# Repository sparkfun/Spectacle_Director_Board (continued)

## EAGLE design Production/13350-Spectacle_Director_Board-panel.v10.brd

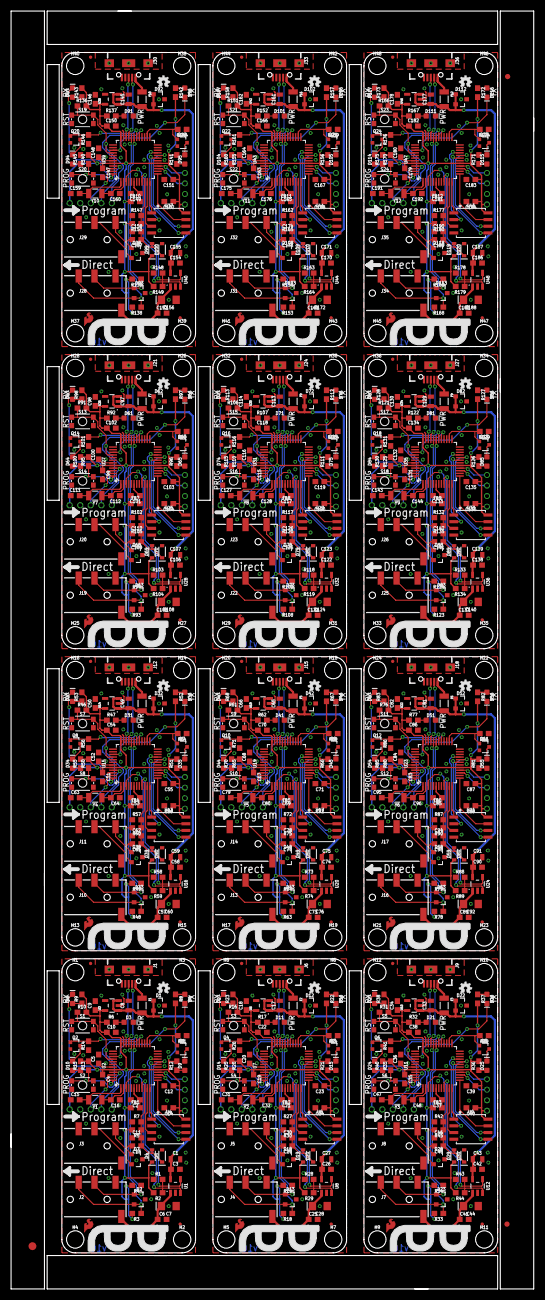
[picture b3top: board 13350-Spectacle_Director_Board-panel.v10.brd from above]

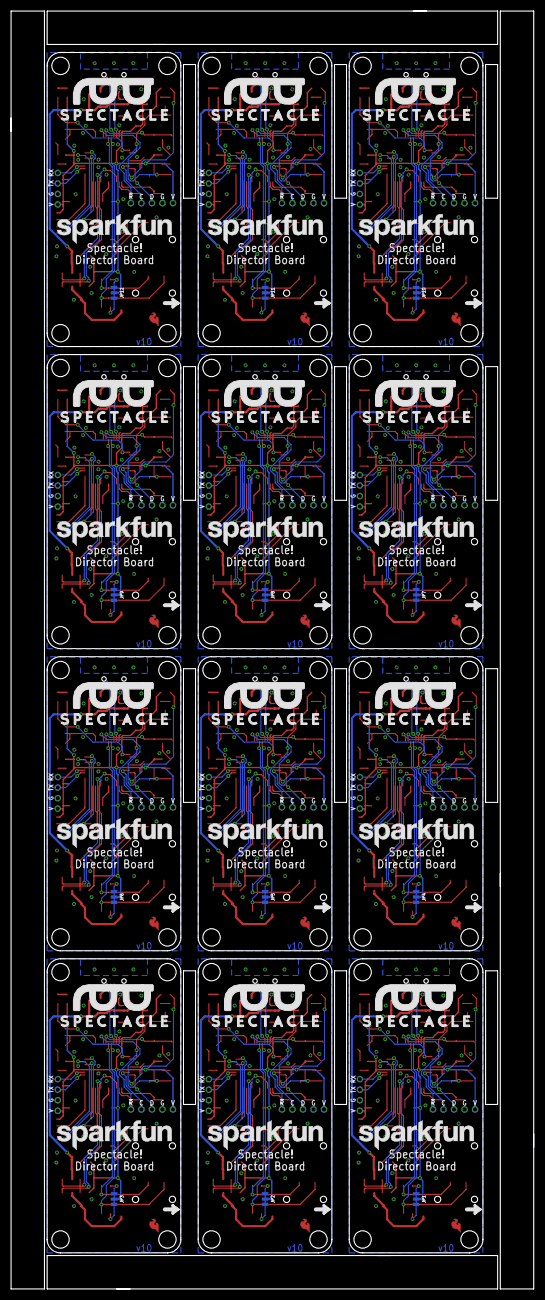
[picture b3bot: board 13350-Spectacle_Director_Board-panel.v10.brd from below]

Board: 2 copper layers, 99.3 x 242.8 mm, 891 parts (132 on the bottom side), 528 nets.

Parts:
C1, C27, C43, C59, C75, C91, C107, C123, C139, C155, C171, C187: 10uF; 0805
C2, C3, C4, C5, C6, C10, C12, C14, C19, C20, C21, C22, C23, C24, C25, C26, C35, C36, C37, C38, C39, C40, C41, C42, C51, C52, C53, C54, C55, C56, C57, C58, C67, C68, C69, C70, C71, C72, C73, C74, C83, C84, C85, C86, C87, C88, C89, C90, C99, C100, C101, C102, C103, C104, C105, C106, C115, C116, C117, C118, C119, C120, C121, C122, C131, C132, C133, C134, C135, C136, C137, C138, C147, C148, C149, C150, C151, C152, C153, C154, C163, C164, C165, C166, C167, C168, C169, C170, C179, C180, C181, C182, C183, C184, C185, C186: 0.1uF; 0603
C7, C28, C44, C60, C76, C92, C108, C124, C140, C156, C172, C188: 10uF; EIA3216
C8, C17, C33, C49, C65, C81, C97, C113, C129, C145, C161, C177: 1.0uF; 0805
C9, C18, C34, C50, C66, C82, C98, C114, C130, C146, C162, C178: 2.2uF; 0603
C11, C30, C46, C62, C78, C94, C110, C126, C142, C158, C174, C190: 47pF; 0603
C13, C29, C45, C61, C77, C93, C109, C125, C141, C157, C173, C189: 0.22uF; 0603
C15, C16, C31, C32, C47, C48, C63, C64, C79, C80, C95, C96, C111, C112, C127, C128, C143, C144, C159, C160, C175, C176, C191, C192: 15pF; 0603
D1, D2, D7, D12, D13, D18, D22, D23, D28, D32, D33, D38, D42, D43, D48, D52, D53, D58, D62, D63, D68, D72, D73, D78, D82, D83, D88, D92, D93, D98, D102, D103, D108, D112, D113, D118: PESD1CAN; SOT23-3
D3, D11, D21, D31, D41, D51, D61, D71, D81, D91, D101, D111: RED; LED-0603
D4, D5, D19, D20, D29, D30, D39, D40, D49, D50, D59, D60, D69, D70, D79, D80, D89, D90, D99, D100, D109, D110, D119, D120: 0.5A/40V/420mV; SOD-323
D6, D10, D14, D16, D24, D26, D34, D36, D44, D46, D54, D56, D64, D66, D74, D76, D84, D86, D94, D96, D104, D106, D114, D116: GREEN; LED-0603
D8, D17, D27, D37, D47, D57, D67, D77, D87, D97, D107, D117: Yellow; LED-0603
D9, D15, D25, D35, D45, D55, D65, D75, D85, D95, D105, D115: BLUE; LED-0603
E$1: FIDUCIAL-1.5X3
E$4, E$7: FIDUCIAL-1X2
F1, F2, F3, F4, F5, F6, F7, F8, F9, F10, F11, F12: 500mA; PTC-1206
FB1, FB2, FB3, FB4, FB5, FB6, FB7, FB8, FB9, FB10, FB11, FB12: 30Ω/1.8A; 0603
FD1, FD2, FD3, FD4, FD5, FD6, FD7, FD8, FD9, FD10, FD11, FD12, FD13, FD14, FD15, FD16, FD17, FD18, FD19, FD20, FD21, FD22, FD23, FD24: FIDUCIALUFIDUCIAL; FIDUCIAL-MICRO
H1, H2, H3, H4, H5, H6, H7, H8, H9, H10, H11, H12, H13, H14, H15, H16, H17, H18, H19, H20, H21, H22, H23, H24, H25, H26, H27, H28, H29, H30, H31, H32, H33, H34, H35, H36, H37, H38, H39, H40, H41, H42, H43, H44, H45, H46, H47, H48: STAND-OFF
J1, J6, J9, J12, J15, J18, J21, J24, J27, J30, J33, J36: USB-B-MICRO-SMD
J2, J4, J7, J10, J13, J16, J19, J22, J25, J28, J31, J34: I2C-TRRS; AUDIO_JACK_3.5MM_TRRS_SMD_RA
J3, J5, J8, J11, J14, J17, J20, J23, J26, J29, J32, J35: Serial-TRRS; AUDIO_JACK_3.5MM_TRRS_SMD_RA
JP1, JP2, JP3, JP4, JP5, JP6, JP7, JP8, JP9, JP10, JP11, JP12: JUMPER-SMT_3_2-NC_TRACE_NO-SILK; SMT-JUMPER_3_2-NC_TRACE_NO-SILK
LOGO1, LOGO5, LOGO8, LOGO11, LOGO14, LOGO17, LOGO20, LOGO23, LOGO26, LOGO29, LOGO32, LOGO35: OSHW-LOGOMINI; OSHW-LOGO-MINI
LOGO2, LOGO4, LOGO7, LOGO10, LOGO13, LOGO16, LOGO19, LOGO22, LOGO25, LOGO28, LOGO31, LOGO34: SFE_LOGO_NAME.2_INCH; SFE_LOGO_NAME_.2
LOGO3, LOGO6, LOGO9, LOGO12, LOGO15, LOGO18, LOGO21, LOGO24, LOGO27, LOGO30, LOGO33, LOGO36: SFE_LOGO_FLAME.1COP; SFE_LOGO_FLAME_COPPER_.1
Q1, Q2, Q3, Q4, Q5, Q6, Q7, Q8, Q9, Q10, Q11, Q12, Q13, Q14, Q15, Q16, Q17, Q18, Q19, Q20, Q21, Q22, Q23, Q24: 310mA/60V/1.6Ω; SOT323
R1, R11, R14, R24, R26, R28, R39, R41, R43, R54, R56, R58, R69, R71, R73, R84, R86, R88, R99, R101, R103, R114, R116, R118, R129, R131, R133, R144, R146, R148, R159, R161, R163, R174, R176, R178: 100k; 0603
R2, R5, R7, R10, R13, R16, R20, R27, R29, R30, R31, R35, R42, R44, R45, R46, R50, R57, R59, R60, R61, R65, R72, R74, R75, R76, R80, R87, R89, R90, R91, R95, R102, R104, R105, R106, R110, R117, R119, R120, R121, R125, R132, R134, R135, R136, R140, R147, R149, R150, R151, R155, R162, R164, R165, R166, R170, R177, R179, R180: 10k; 0603
R3, R4, R18, R19, R33, R34, R48, R49, R63, R64, R78, R79, R93, R94, R108, R109, R123, R124, R138, R139, R153, R154, R168, R169: 2.2k; 0603
R6, R17, R32, R47, R62, R77, R92, R107, R122, R137, R152, R167: 1k; 0603
R8, R9, R12, R15, R21, R22, R23, R25, R36, R37, R38, R40, R51, R52, R53, R55, R66, R67, R68, R70, R81, R82, R83, R85, R96, R97, R98, R100, R111, R112, R113, R115, R126, R127, R128, R130, R141, R142, R143, R145, R156, R157, R158, R160, R171, R172, R173, R175: 330; 0603
S1, S3, S5, S7, S9, S11, S13, S15, S17, S19, S21, S23: RESET; TACTILE_SWITCH_SMD_4.6X2.8MM
S2, S4, S6, S8, S10, S12, S14, S16, S18, S20, S22, S24: BTN2; TACTILE_SWITCH_SMD_4.6X2.8MM
TP1, TP10, TP19, TP28, TP37, TP46, TP55, TP64, TP73, TP82, TP91, TP100: TP-SWDIO; PAD.03X.05
TP2, TP11, TP20, TP29, TP38, TP47, TP56, TP65, TP74, TP83, TP92, TP101: TP-SWCLK; PAD.03X.05
TP3, TP12, TP21, TP30, TP39, TP48, TP57, TP66, TP75, TP84, TP93, TP102: TP-!RESET!; PAD.03X.05
TP4, TP13, TP22, TP31, TP40, TP49, TP58, TP67, TP76, TP85, TP94, TP103: TP-3.3V; PAD.03X.05
TP5, TP6, TP7, TP8, TP9, TP14, TP15, TP16, TP17, TP18, TP23, TP24, TP25, TP26, TP27, TP32, TP33, TP34, TP35, TP36, TP41, TP42, TP43, TP44, TP45, TP50, TP51, TP52, TP53, TP54, TP59, TP60, TP61, TP62, TP63, TP68, TP69, TP70, TP71, TP72, TP77, TP78, TP79, TP80, TP81, TP86, TP87, TP88, TP89, TP90, TP95, TP96, TP97, TP98, TP99, TP104, TP105, TP106, TP107, TP108: TP-GND; PAD.03X.05
U1, U8, U12, U16, U20, U24, U28, U32, U36, U40, U44, U48: AP2151; SOT23-5
U2, U7, U11, U15, U19, U23, U27, U31, U35, U39, U43, U47: ATSAMD21G-A; TQFP-48
U3, U6, U10, U14, U18, U22, U26, U30, U34, U38, U42, U46: 3.3V; SOT23-5
U4, U5, U9, U13, U17, U21, U25, U29, U33, U37, U41, U45: W25Q32FV; SOIC-8
Y1, Y2, Y3, Y4, Y5, Y6, Y7, Y8, Y9, Y10, Y11, Y12: 32.768kHz; CRYSTAL-SMD-3.2X1.5MM

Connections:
3.3V: C4.1, C9.1, C10.1, C12.1, C14.1, D4.C, FB1.1, JP1.2, R2.2, R5.2, R6.1, R8.2, R9.2, R10.2, R12.2, R13.2, R15.2, TP4.P$1, TP6.P$1, U2.17, U2.36, U2.44, U3.5, U4.8
3.3V1: C18.1, C19.1, C22.1, C23.1, C24.1, D19.C, FB2.1, JP2.2, R16.2, R17.1, R20.2, R21.2, R22.2, R23.2, R25.2, R29.2, R30.2, TP13.P$1, TP15.P$1, U5.8, U6.5, U7.17, U7.36, U7.44
3.3V2: C34.1, C35.1, C38.1, C39.1, C40.1, D29.C, FB3.1, JP3.2, R31.2, R32.1, R35.2, R36.2, R37.2, R38.2, R40.2, R44.2, R45.2, TP22.P$1, TP24.P$1, U9.8, U10.5, U11.17, U11.36, U11.44
3.3V3: C50.1, C51.1, C54.1, C55.1, C56.1, D39.C, FB4.1, JP4.2, R46.2, R47.1, R50.2, R51.2, R52.2, R53.2, R55.2, R59.2, R60.2, TP31.P$1, TP33.P$1, U13.8, U14.5, U15.17, U15.36, U15.44
3.3V4: C66.1, C67.1, C70.1, C71.1, C72.1, D49.C, FB5.1, JP5.2, R61.2, R62.1, R65.2, R66.2, R67.2, R68.2, R70.2, R74.2, R75.2, TP40.P$1, TP42.P$1, U17.8, U18.5, U19.17, U19.36, U19.44
3.3V5: C82.1, C83.1, C86.1, C87.1, C88.1, D59.C, FB6.1, JP6.2, R76.2, R77.1, R80.2, R81.2, R82.2, R83.2, R85.2, R89.2, R90.2, TP49.P$1, TP51.P$1, U21.8, U22.5, U23.17, U23.36, U23.44
3.3V6: C98.1, C99.1, C102.1, C103.1, C104.1, D69.C, FB7.1, JP7.2, R91.2, R92.1, R95.2, R96.2, R97.2, R98.2, R100.2, R104.2, R105.2, TP58.P$1, TP60.P$1, U25.8, U26.5, U27.17, U27.36, U27.44
3.3V7: C114.1, C115.1, C118.1, C119.1, C120.1, D79.C, FB8.1, JP8.2, R106.2, R107.1, R110.2, R111.2, R112.2, R113.2, R115.2, R119.2, R120.2, TP67.P$1, TP69.P$1, U29.8, U30.5, U31.17, U31.36, U31.44
3.3V8: C130.1, C131.1, C134.1, C135.1, C136.1, D89.C, FB9.1, JP9.2, R121.2, R122.1, R125.2, R126.2, R127.2, R128.2, R130.2, R134.2, R135.2, TP76.P$1, TP78.P$1, U33.8, U34.5, U35.17, U35.36, U35.44
3.3V9: C146.1, C147.1, C150.1, C151.1, C152.1, D99.C, FB10.1, JP10.2, R136.2, R137.1, R140.2, R141.2, R142.2, R143.2, R145.2, R149.2, R150.2, TP85.P$1, TP87.P$1, U37.8, U38.5, U39.17, U39.36, U39.44
3.3V10: C162.1, C163.1, C166.1, C167.1, C168.1, D109.C, FB11.1, JP11.2, R151.2, R152.1, R155.2, R156.2, R157.2, R158.2, R160.2, R164.2, R165.2, TP94.P$1, TP96.P$1, U41.8, U42.5, U43.17, U43.36, U43.44
3.3V11: C178.1, C179.1, C182.1, C183.1, C184.1, D119.C, FB12.1, JP12.2, R166.2, R167.1, R170.2, R171.2, R172.2, R173.2, R175.2, R179.2, R180.2, TP103.P$1, TP105.P$1, U45.8, U46.5, U47.17, U47.36, U47.44
!RESET: R10.1, S1.3, S1.4, TP3.P$1, U2.40
!RESET1: R16.1, S3.3, S3.4, TP12.P$1, U7.40
!RESET2: R31.1, S5.3, S5.4, TP21.P$1, U11.40
!RESET3: R46.1, S7.3, S7.4, TP30.P$1, U15.40
!RESET4: R61.1, S9.3, S9.4, TP39.P$1, U19.40
!RESET5: R76.1, S11.3, S11.4, TP48.P$1, U23.40
!RESET6: R91.1, S13.3, S13.4, TP57.P$1, U27.40
!RESET7: R106.1, S15.3, S15.4, TP66.P$1, U31.40
!RESET8: R121.1, S17.3, S17.4, TP75.P$1, U35.40
!RESET9: R136.1, S19.3, S19.4, TP84.P$1, U39.40
!RESET10: R151.1, S21.3, S21.4, TP93.P$1, U43.40
!RESET11: R166.1, S23.3, S23.4, TP102.P$1, U47.40
A1_FSK-RX: C11.2, C13.1, D4.A, D5.C, R5.1, R7.2, U2.10
A1_FSK-RX1: C29.1, C30.2, D19.A, D20.C, R27.2, R30.1, U7.10
A1_FSK-RX2: C45.1, C46.2, D29.A, D30.C, R42.2, R45.1, U11.10
A1_FSK-RX3: C61.1, C62.2, D39.A, D40.C, R57.2, R60.1, U15.10
A1_FSK-RX4: C77.1, C78.2, D49.A, D50.C, R72.2, R75.1, U19.10
A1_FSK-RX5: C93.1, C94.2, D59.A, D60.C, R87.2, R90.1, U23.10
A1_FSK-RX6: C109.1, C110.2, D69.A, D70.C, R102.2, R105.1, U27.10
A1_FSK-RX7: C125.1, C126.2, D79.A, D80.C, R117.2, R120.1, U31.10
A1_FSK-RX8: C141.1, C142.2, D89.A, D90.C, R132.2, R135.1, U35.10
A1_FSK-RX9: C157.1, C158.2, D99.A, D100.C, R147.2, R150.1, U39.10
A1_FSK-RX10: C173.1, C174.2, D109.A, D110.C, R162.2, R165.1, U43.10
A1_FSK-RX11: C189.1, C190.2, D119.A, D120.C, R177.2, R180.1, U47.10
A3_VOUT_EN: R1.2, U1.4, U2.9
A3_VOUT_EN1: R28.2, U7.9, U8.4
A3_VOUT_EN2: R43.2, U11.9, U12.4
A3_VOUT_EN3: R58.2, U15.9, U16.4
A3_VOUT_EN4: R73.2, U19.9, U20.4
A3_VOUT_EN5: R88.2, U23.9, U24.4
A3_VOUT_EN6: R103.2, U27.9, U28.4
A3_VOUT_EN7: R118.2, U31.9, U32.4
A3_VOUT_EN8: R133.2, U35.9, U36.4
A3_VOUT_EN9: R148.2, U39.9, U40.4
A3_VOUT_EN10: R163.2, U43.9, U44.4
A3_VOUT_EN11: R178.2, U47.9, U48.4
A4_VOUT_FLG: R2.1, U1.3, U2.3
A4_VOUT_FLG1: R29.1, U7.3, U8.3
A4_VOUT_FLG2: R44.1, U11.3, U12.3
A4_VOUT_FLG3: R59.1, U15.3, U16.3
A4_VOUT_FLG4: R74.1, U19.3, U20.3
A4_VOUT_FLG5: R89.1, U23.3, U24.3
A4_VOUT_FLG6: R104.1, U27.3, U28.3
A4_VOUT_FLG7: R119.1, U31.3, U32.3
A4_VOUT_FLG8: R134.1, U35.3, U36.3
A4_VOUT_FLG9: R149.1, U39.3, U40.3
A4_VOUT_FLG10: R164.1, U43.3, U44.3
A4_VOUT_FLG11: R179.1, U47.3, U48.3
D0/RXI: TP8.P$1, U2.16
D0/RXI1: TP17.P$1, U7.16
D0/RXI2: TP26.P$1, U11.16
D0/RXI3: TP35.P$1, U15.16
D0/RXI4: TP44.P$1, U19.16
D0/RXI5: TP53.P$1, U23.16
D0/RXI6: TP62.P$1, U27.16
D0/RXI7: TP71.P$1, U31.16
D0/RXI8: TP80.P$1, U35.16
D0/RXI9: TP89.P$1, U39.16
D0/RXI10: TP98.P$1, U43.16
D0/RXI11: TP107.P$1, U47.16
D1/TXO: TP7.P$1, U2.15
D1/TXO1: TP16.P$1, U7.15
D1/TXO2: TP25.P$1, U11.15
D1/TXO3: TP34.P$1, U15.15
D1/TXO4: TP43.P$1, U19.15
D1/TXO5: TP52.P$1, U23.15
D1/TXO6: TP61.P$1, U27.15
D1/TXO7: TP70.P$1, U31.15
D1/TXO8: TP79.P$1, U35.15
D1/TXO9: TP88.P$1, U39.15
D1/TXO10: TP97.P$1, U43.15
D1/TXO11: TP106.P$1, U47.15
D4_FLASH!HD!: U2.13, U4.7
D4_FLASH!HD!1: U5.7, U7.13
D4_FLASH!HD!2: U9.7, U11.13
D4_FLASH!HD!3: U13.7, U15.13
D4_FLASH!HD!4: U17.7, U19.13
D4_FLASH!HD!5: U21.7, U23.13
D4_FLASH!HD!6: U25.7, U27.13
D4_FLASH!HD!7: U29.7, U31.13
D4_FLASH!HD!8: U33.7, U35.13
D4_FLASH!HD!9: U37.7, U39.13
D4_FLASH!HD!10: U41.7, U43.13
D4_FLASH!HD!11: U45.7, U47.13
D6_BTN: R13.1, S2.3, S2.4, U2.29
D6_BTN1: R20.1, S4.3, S4.4, U7.29
D6_BTN2: R35.1, S6.3, S6.4, U11.29
D6_BTN3: R50.1, S8.3, S8.4, U15.29
D6_BTN4: R65.1, S10.3, S10.4, U19.29
D6_BTN5: R80.1, S12.3, S12.4, U23.29
D6_BTN6: R95.1, S14.3, S14.4, U27.29
D6_BTN7: R110.1, S16.3, S16.4, U31.29
D6_BTN8: R125.1, S18.3, S18.4, U35.29
D6_BTN9: R140.1, S20.3, S20.4, U39.29
D6_BTN10: R155.1, S22.3, S22.4, U43.29
D6_BTN11: R170.1, S24.3, S24.4, U47.29
D7_LED1: Q4.1, R26.2, U7.30
D7_LED2: Q2.1, R14.2, U2.30
D7_LED3: Q6.1, R41.2, U11.30
D7_LED4: Q8.1, R56.2, U15.30
D7_LED5: Q10.1, R71.2, U19.30
D7_LED6: Q12.1, R86.2, U23.30
D7_LED7: Q14.1, R101.2, U27.30
D7_LED8: Q16.1, R116.2, U31.30
D7_LED9: Q18.1, R131.2, U35.30
D7_LED10: Q20.1, R146.2, U39.30
D7_LED11: Q22.1, R161.2, U43.30
D7_LED12: Q24.1, R176.2, U47.30
D8_FLASH!WP!: U2.11, U4.3
D8_FLASH!WP!1: U5.3, U7.11
D8_FLASH!WP!2: U9.3, U11.11
D8_FLASH!WP!3: U13.3, U15.11
D8_FLASH!WP!4: U17.3, U19.11
D8_FLASH!WP!5: U21.3, U23.11
D8_FLASH!WP!6: U25.3, U27.11
D8_FLASH!WP!7: U29.3, U31.11
D8_FLASH!WP!8: U33.3, U35.11
D8_FLASH!WP!9: U37.3, U39.11
D8_FLASH!WP!10: U41.3, U43.11
D8_FLASH!WP!11: U45.3, U47.11
D9_FLASH!CS!: U2.12, U4.1
D9_FLASH!CS!1: U5.1, U7.12
D9_FLASH!CS!2: U9.1, U11.12
D9_FLASH!CS!3: U13.1, U15.12
D9_FLASH!CS!4: U17.1, U19.12
D9_FLASH!CS!5: U21.1, U23.12
D9_FLASH!CS!6: U25.1, U27.12
D9_FLASH!CS!7: U29.1, U31.12
D9_FLASH!CS!8: U33.1, U35.12
D9_FLASH!CS!9: U37.1, U39.12
D9_FLASH!CS!10: U41.1, U43.12
D9_FLASH!CS!11: U45.1, U47.12
D13_LED1: Q1.1, R11.2, U2.26
D13_LED2: Q3.1, R24.2, U7.26
D13_LED3: Q5.1, R39.2, U11.26
D13_LED4: Q7.1, R54.2, U15.26
D13_LED5: Q9.1, R69.2, U19.26
D13_LED6: Q11.1, R84.2, U23.26
D13_LED7: Q13.1, R99.2, U27.26
D13_LED8: Q15.1, R114.2, U31.26
D13_LED9: Q17.1, R129.2, U35.26
D13_LED10: Q19.1, R144.2, U39.26
D13_LED11: Q21.1, R159.2, U43.26
D13_LED12: Q23.1, R174.2, U47.26
GND: C1.2, C2.2, C3.2, C4.2, C5.2, C6.2, C7.-, C8.2, C9.2, C10.2, C11.1, C12.2, C14.2, C15.1, C16.1, D1.3, D2.3, D3.C, D5.A, D7.3, J1.GND, J2.TIP, J3.EARTH, J3.RING2, Q1.2, Q2.2, R1.1, R7.1, R11.1, R14.1, S1.1, S1.2, S2.1, S2.2, TP5.P$1, TP9.P$1, U1.2, U2.5, U2.18, U2.35, U2.42, U3.2, U4.4
GND1: C17.2, C18.2, C19.2, C20.2, C21.2, C22.2, C23.2, C24.2, C25.2, C26.2, C27.2, C28.-, C30.1, C31.1, C32.1, D11.C, D12.3, D13.3, D18.3, D20.A, J4.TIP, J5.EARTH, J5.RING2, J6.GND, Q3.2, Q4.2, R24.1, R26.1, R27.1, R28.1, S3.1, S3.2, S4.1, S4.2, TP14.P$1, TP18.P$1, U5.4, U6.2, U7.5, U7.18, U7.35, U7.42, U8.2
GND2: C33.2, C34.2, C35.2, C36.2, C37.2, C38.2, C39.2, C40.2, C41.2, C42.2, C43.2, C44.-, C46.1, C47.1, C48.1, D21.C, D22.3, D23.3, D28.3, D30.A, J7.TIP, J8.EARTH, J8.RING2, J9.GND, Q5.2, Q6.2, R39.1, R41.1, R42.1, R43.1, S5.1, S5.2, S6.1, S6.2, TP23.P$1, TP27.P$1, U9.4, U10.2, U11.5, U11.18, U11.35, U11.42, U12.2
GND3: C49.2, C50.2, C51.2, C52.2, C53.2, C54.2, C55.2, C56.2, C57.2, C58.2, C59.2, C60.-, C62.1, C63.1, C64.1, D31.C, D32.3, D33.3, D38.3, D40.A, J10.TIP, J11.EARTH, J11.RING2, J12.GND, Q7.2, Q8.2, R54.1, R56.1, R57.1, R58.1, S7.1, S7.2, S8.1, S8.2, TP32.P$1, TP36.P$1, U13.4, U14.2, U15.5, U15.18, U15.35, U15.42, U16.2
GND4: C65.2, C66.2, C67.2, C68.2, C69.2, C70.2, C71.2, C72.2, C73.2, C74.2, C75.2, C76.-, C78.1, C79.1, C80.1, D41.C, D42.3, D43.3, D48.3, D50.A, J13.TIP, J14.EARTH, J14.RING2, J15.GND, Q9.2, Q10.2, R69.1, R71.1, R72.1, R73.1, S9.1, S9.2, S10.1, S10.2, TP41.P$1, TP45.P$1, U17.4, U18.2, U19.5, U19.18, U19.35, U19.42, U20.2
GND5: C81.2, C82.2, C83.2, C84.2, C85.2, C86.2, C87.2, C88.2, C89.2, C90.2, C91.2, C92.-, C94.1, C95.1, C96.1, D51.C, D52.3, D53.3, D58.3, D60.A, J16.TIP, J17.EARTH, J17.RING2, J18.GND, Q11.2, Q12.2, R84.1, R86.1, R87.1, R88.1, S11.1, S11.2, S12.1, S12.2, TP50.P$1, TP54.P$1, U21.4, U22.2, U23.5, U23.18, U23.35, U23.42, U24.2
GND6: C97.2, C98.2, C99.2, C100.2, C101.2, C102.2, C103.2, C104.2, C105.2, C106.2, C107.2, C108.-, C110.1, C111.1, C112.1, D61.C, D62.3, D63.3, D68.3, D70.A, J19.TIP, J20.EARTH, J20.RING2, J21.GND, Q13.2, Q14.2, R99.1, R101.1, R102.1, R103.1, S13.1, S13.2, S14.1, S14.2, TP59.P$1, TP63.P$1, U25.4, U26.2, U27.5, U27.18, U27.35, U27.42, U28.2
GND7: C113.2, C114.2, C115.2, C116.2, C117.2, C118.2, C119.2, C120.2, C121.2, C122.2, C123.2, C124.-, C126.1, C127.1, C128.1, D71.C, D72.3, D73.3, D78.3, D80.A, J22.TIP, J23.EARTH, J23.RING2, J24.GND, Q15.2, Q16.2, R114.1, R116.1, R117.1, R118.1, S15.1, S15.2, S16.1, S16.2, TP68.P$1, TP72.P$1, U29.4, U30.2, U31.5, U31.18, U31.35, U31.42, U32.2
GND8: C129.2, C130.2, C131.2, C132.2, C133.2, C134.2, C135.2, C136.2, C137.2, C138.2, C139.2, C140.-, C142.1, C143.1, C144.1, D81.C, D82.3, D83.3, D88.3, D90.A, J25.TIP, J26.EARTH, J26.RING2, J27.GND, Q17.2, Q18.2, R129.1, R131.1, R132.1, R133.1, S17.1, S17.2, S18.1, S18.2, TP77.P$1, TP81.P$1, U33.4, U34.2, U35.5, U35.18, U35.35, U35.42, U36.2
GND9: C145.2, C146.2, C147.2, C148.2, C149.2, C150.2, C151.2, C152.2, C153.2, C154.2, C155.2, C156.-, C158.1, C159.1, C160.1, D91.C, D92.3, D93.3, D98.3, D100.A, J28.TIP, J29.EARTH, J29.RING2, J30.GND, Q19.2, Q20.2, R144.1, R146.1, R147.1, R148.1, S19.1, S19.2, S20.1, S20.2, TP86.P$1, TP90.P$1, U37.4, U38.2, U39.5, U39.18, U39.35, U39.42, U40.2
GND10: C161.2, C162.2, C163.2, C164.2, C165.2, C166.2, C167.2, C168.2, C169.2, C170.2, C171.2, C172.-, C174.1, C175.1, C176.1, D101.C, D102.3, D103.3, D108.3, D110.A, J31.TIP, J32.EARTH, J32.RING2, J33.GND, Q21.2, Q22.2, R159.1, R161.1, R162.1, R163.1, S21.1, S21.2, S22.1, S22.2, TP95.P$1, TP99.P$1, U41.4, U42.2, U43.5, U43.18, U43.35, U43.42, U44.2
GND11: C177.2, C178.2, C179.2, C180.2, C181.2, C182.2, C183.2, C184.2, C185.2, C186.2, C187.2, C188.-, C190.1, C191.1, C192.1, D111.C, D112.3, D113.3, D118.3, D120.A, J34.TIP, J35.EARTH, J35.RING2, J36.GND, Q23.2, Q24.2, R174.1, R176.1, R177.1, R178.1, S23.1, S23.2, S24.1, S24.2, TP104.P$1, TP108.P$1, U45.4, U46.2, U47.5, U47.18, U47.35, U47.42, U48.2
unnamed: D10.A, R15.1
unnamed: D3.A, R6.2
unnamed: C15.2, U2.1, Y1.P$2
unnamed: JP1.3, R3.2
unnamed: JP1.1, R4.2
unnamed: C16.2, U2.2, Y1.P$1
unnamed: D10.C, Q2.3
unnamed: D11.A, R17.2
unnamed: D9.A, R12.1
unnamed: D9.C, Q1.3
unnamed: D6.A, R8.1
unnamed: D8.A, R9.1
unnamed: JP2.3, R18.2
unnamed: JP2.1, R19.2
unnamed: D15.A, R21.1
unnamed: D15.C, Q3.3
unnamed: D16.A, R22.1
unnamed: D17.A, R23.1
unnamed: D14.A, R25.1
unnamed: D14.C, Q4.3
unnamed: C31.2, U7.1, Y2.P$2
unnamed: C32.2, U7.2, Y2.P$1
unnamed: D21.A, R32.2
unnamed: JP3.3, R33.2
unnamed: JP3.1, R34.2
unnamed: D25.A, R36.1
unnamed: D25.C, Q5.3
unnamed: D26.A, R37.1
unnamed: D27.A, R38.1
unnamed: D24.A, R40.1
unnamed: D24.C, Q6.3
unnamed: C47.2, U11.1, Y3.P$2
unnamed: C48.2, U11.2, Y3.P$1
unnamed: D31.A, R47.2
unnamed: JP4.3, R48.2
unnamed: JP4.1, R49.2
unnamed: D35.A, R51.1
unnamed: D35.C, Q7.3
unnamed: D36.A, R52.1
unnamed: D37.A, R53.1
unnamed: D34.A, R55.1
unnamed: D34.C, Q8.3
unnamed: C63.2, U15.1, Y4.P$2
unnamed: C64.2, U15.2, Y4.P$1
unnamed: D41.A, R62.2
unnamed: JP5.3, R63.2
unnamed: JP5.1, R64.2
unnamed: D45.A, R66.1
unnamed: D45.C, Q9.3
unnamed: D46.A, R67.1
unnamed: D47.A, R68.1
unnamed: D44.A, R70.1
unnamed: D44.C, Q10.3
unnamed: C79.2, U19.1, Y5.P$2
unnamed: C80.2, U19.2, Y5.P$1
unnamed: D51.A, R77.2
unnamed: JP6.3, R78.2
unnamed: JP6.1, R79.2
unnamed: D55.A, R81.1
unnamed: D55.C, Q11.3
unnamed: D56.A, R82.1
unnamed: D57.A, R83.1
unnamed: D54.A, R85.1
unnamed: D54.C, Q12.3
unnamed: C95.2, U23.1, Y6.P$2
unnamed: C96.2, U23.2, Y6.P$1
unnamed: D61.A, R92.2
unnamed: JP7.3, R93.2
unnamed: JP7.1, R94.2
unnamed: D65.A, R96.1
unnamed: D65.C, Q13.3
unnamed: D66.A, R97.1
unnamed: D67.A, R98.1
unnamed: D64.A, R100.1
unnamed: D64.C, Q14.3
unnamed: C111.2, U27.1, Y7.P$2
unnamed: C112.2, U27.2, Y7.P$1
unnamed: D71.A, R107.2
unnamed: JP8.3, R108.2
unnamed: JP8.1, R109.2
unnamed: D75.A, R111.1
unnamed: D75.C, Q15.3
unnamed: D76.A, R112.1
unnamed: D77.A, R113.1
unnamed: D74.A, R115.1
unnamed: D74.C, Q16.3
unnamed: C127.2, U31.1, Y8.P$2
unnamed: C128.2, U31.2, Y8.P$1
unnamed: D81.A, R122.2
unnamed: JP9.3, R123.2
unnamed: JP9.1, R124.2
unnamed: D85.A, R126.1
unnamed: D85.C, Q17.3
unnamed: D86.A, R127.1
unnamed: D87.A, R128.1
unnamed: D84.A, R130.1
unnamed: D84.C, Q18.3
unnamed: C143.2, U35.1, Y9.P$2
unnamed: C144.2, U35.2, Y9.P$1
unnamed: D91.A, R137.2
unnamed: JP10.3, R138.2
unnamed: JP10.1, R139.2
unnamed: D95.A, R141.1
unnamed: D95.C, Q19.3
unnamed: D96.A, R142.1
unnamed: D97.A, R143.1
unnamed: D94.A, R145.1
unnamed: D94.C, Q20.3
unnamed: C159.2, U39.1, Y10.P$2
unnamed: C160.2, U39.2, Y10.P$1
unnamed: D101.A, R152.2
unnamed: JP11.3, R153.2
unnamed: JP11.1, R154.2
unnamed: D105.A, R156.1
unnamed: D105.C, Q21.3
unnamed: D106.A, R157.1
unnamed: D107.A, R158.1
unnamed: D104.A, R160.1
unnamed: D104.C, Q22.3
unnamed: C175.2, U43.1, Y11.P$2
unnamed: C176.2, U43.2, Y11.P$1
unnamed: D111.A, R167.2
unnamed: JP12.3, R168.2
unnamed: JP12.1, R169.2
unnamed: D115.A, R171.1
unnamed: D115.C, Q23.3
unnamed: D116.A, R172.1
unnamed: D117.A, R173.1
unnamed: D114.A, R175.1
unnamed: D114.C, Q24.3
unnamed: C191.2, U47.1, Y12.P$2
unnamed: C192.2, U47.2, Y12.P$1
RING1-RIGHT: D7.2, J3.RING1
RING1-RIGHT1: D18.2, J5.RING1
RING1-RIGHT2: D28.2, J8.RING1
RING1-RIGHT3: D38.2, J11.RING1
RING1-RIGHT4: D48.2, J14.RING1
RING1-RIGHT5: D58.2, J17.RING1
RING1-RIGHT6: D68.2, J20.RING1
RING1-RIGHT7: D78.2, J23.RING1
RING1-RIGHT8: D88.2, J26.RING1
RING1-RIGHT9: D98.2, J29.RING1
RING1-RIGHT10: D108.2, J32.RING1
RING1-RIGHT11: D118.2, J35.RING1
RX_LED: D8.C, U2.48
RX_LED1: D17.C, U7.48
RX_LED2: D27.C, U11.48
RX_LED3: D37.C, U15.48
RX_LED4: D47.C, U19.48
RX_LED5: D57.C, U23.48
RX_LED6: D67.C, U27.48
RX_LED7: D77.C, U31.48
RX_LED8: D87.C, U35.48
RX_LED9: D97.C, U39.48
RX_LED10: D107.C, U43.48
RX_LED11: D117.C, U47.48
SCL: D2.2, J2.RING2, R3.1, U2.32
SCL1: D13.2, J4.RING2, R18.1, U7.32
SCL2: D23.2, J7.RING2, R33.1, U11.32
SCL3: D33.2, J10.RING2, R48.1, U15.32
SCL4: D43.2, J13.RING2, R63.1, U19.32
SCL5: D53.2, J16.RING2, R78.1, U23.32
SCL6: D63.2, J19.RING2, R93.1, U27.32
SCL7: D73.2, J22.RING2, R108.1, U31.32
SCL8: D83.2, J25.RING2, R123.1, U35.32
SCL9: D93.2, J28.RING2, R138.1, U39.32
SCL10: D103.2, J31.RING2, R153.1, U43.32
SCL11: D113.2, J34.RING2, R168.1, U47.32
SDA: D2.1, J2.RING1, R4.1, U2.31
SDA1: D13.1, J4.RING1, R19.1, U7.31
SDA2: D23.1, J7.RING1, R34.1, U11.31
SDA3: D33.1, J10.RING1, R49.1, U15.31
SDA4: D43.1, J13.RING1, R64.1, U19.31
SDA5: D53.1, J16.RING1, R79.1, U23.31
SDA6: D63.1, J19.RING1, R94.1, U27.31
SDA7: D73.1, J22.RING1, R109.1, U31.31
SDA8: D83.1, J25.RING1, R124.1, U35.31
SDA9: D93.1, J28.RING1, R139.1, U39.31
SDA10: D103.1, J31.RING1, R154.1, U43.31
SDA11: D113.1, J34.RING1, R169.1, U47.31
SHIELD: J1.SHIELD1, J1.SHIELD2, J1.SHIELD3
SHIELD1: J6.SHIELD1, J6.SHIELD2, J6.SHIELD3
SHIELD2: J9.SHIELD1, J9.SHIELD2, J9.SHIELD3
SHIELD3: J12.SHIELD1, J12.SHIELD2, J12.SHIELD3
SHIELD4: J15.SHIELD1, J15.SHIELD2, J15.SHIELD3
SHIELD5: J18.SHIELD1, J18.SHIELD2, J18.SHIELD3
SHIELD6: J21.SHIELD1, J21.SHIELD2, J21.SHIELD3
SHIELD7: J24.SHIELD1, J24.SHIELD2, J24.SHIELD3
SHIELD8: J27.SHIELD1, J27.SHIELD2, J27.SHIELD3
SHIELD9: J30.SHIELD1, J30.SHIELD2, J30.SHIELD3
SHIELD10: J33.SHIELD1, J33.SHIELD2, J33.SHIELD3
SHIELD11: J36.SHIELD1, J36.SHIELD2, J36.SHIELD3
SPI_MISO: U2.21, U4.2
SPI_MISO1: U5.2, U7.21
SPI_MISO2: U9.2, U11.21
SPI_MISO3: U13.2, U15.21
SPI_MISO4: U17.2, U19.21
SPI_MISO5: U21.2, U23.21
SPI_MISO6: U25.2, U27.21
SPI_MISO7: U29.2, U31.21
SPI_MISO8: U33.2, U35.21
SPI_MISO9: U37.2, U39.21
SPI_MISO10: U41.2, U43.21
SPI_MISO11: U45.2, U47.21
SPI_MOSI: U2.19, U4.5
SPI_MOSI1: U5.5, U7.19
SPI_MOSI2: U9.5, U11.19
SPI_MOSI3: U13.5, U15.19
SPI_MOSI4: U17.5, U19.19
SPI_MOSI5: U21.5, U23.19
SPI_MOSI6: U25.5, U27.19
SPI_MOSI7: U29.5, U31.19
SPI_MOSI8: U33.5, U35.19
SPI_MOSI9: U37.5, U39.19
SPI_MOSI10: U41.5, U43.19
SPI_MOSI11: U45.5, U47.19
SPI_SCK: U2.20, U4.6
SPI_SCK1: U5.6, U7.20
SPI_SCK2: U9.6, U11.20
SPI_SCK3: U13.6, U15.20
SPI_SCK4: U17.6, U19.20
SPI_SCK5: U21.6, U23.20
SPI_SCK6: U25.6, U27.20
SPI_SCK7: U29.6, U31.20
SPI_SCK8: U33.6, U35.20
SPI_SCK9: U37.6, U39.20
SPI_SCK10: U41.6, U43.20
SPI_SCK11: U45.6, U47.20
SWCLK: TP2.P$1, U2.45
SWCLK1: TP11.P$1, U7.45
SWCLK2: TP20.P$1, U11.45
SWCLK3: TP29.P$1, U15.45
SWCLK4: TP38.P$1, U19.45
SWCLK5: TP47.P$1, U23.45
SWCLK6: TP56.P$1, U27.45
SWCLK7: TP65.P$1, U31.45
SWCLK8: TP74.P$1, U35.45
SWCLK9: TP83.P$1, U39.45
SWCLK10: TP92.P$1, U43.45
SWCLK11: TP101.P$1, U47.45
SWDIO: TP1.P$1, U2.46
SWDIO1: TP10.P$1, U7.46
SWDIO2: TP19.P$1, U11.46
SWDIO3: TP28.P$1, U15.46
SWDIO4: TP37.P$1, U19.46
SWDIO5: TP46.P$1, U23.46
SWDIO6: TP55.P$1, U27.46
SWDIO7: TP64.P$1, U31.46
SWDIO8: TP73.P$1, U35.46
SWDIO9: TP82.P$1, U39.46
SWDIO10: TP91.P$1, U43.46
SWDIO11: TP100.P$1, U47.46
TIP-LEFT: C13.2, D7.1, J3.TIP
TIP-LEFT1: C29.2, D18.1, J5.TIP
TIP-LEFT2: C45.2, D28.1, J8.TIP
TIP-LEFT3: C61.2, D38.1, J11.TIP
TIP-LEFT4: C77.2, D48.1, J14.TIP
TIP-LEFT5: C93.2, D58.1, J17.TIP
TIP-LEFT6: C109.2, D68.1, J20.TIP
TIP-LEFT7: C125.2, D78.1, J23.TIP
TIP-LEFT8: C141.2, D88.1, J26.TIP
TIP-LEFT9: C157.2, D98.1, J29.TIP
TIP-LEFT10: C173.2, D108.1, J32.TIP
TIP-LEFT11: C189.2, D118.1, J35.TIP
TX_LED: D6.C, U2.39
TX_LED1: D16.C, U7.39
TX_LED2: D26.C, U11.39
TX_LED3: D36.C, U15.39
TX_LED4: D46.C, U19.39
TX_LED5: D56.C, U23.39
TX_LED6: D66.C, U27.39
TX_LED7: D76.C, U31.39
TX_LED8: D86.C, U35.39
TX_LED9: D96.C, U39.39
TX_LED10: D106.C, U43.39
TX_LED11: D116.C, U47.39
USB_D+: J1.D+, U2.34
USB_D+1: J6.D+, U7.34
USB_D+2: J9.D+, U11.34
USB_D+3: J12.D+, U15.34
USB_D+4: J15.D+, U19.34
USB_D+5: J18.D+, U23.34
USB_D+6: J21.D+, U27.34
USB_D+7: J24.D+, U31.34
USB_D+8: J27.D+, U35.34
USB_D+9: J30.D+, U39.34
USB_D+10: J33.D+, U43.34
USB_D+11: J36.D+, U47.34
USB_D-: J1.D-, U2.33
USB_D-1: J6.D-, U7.33
USB_D-2: J9.D-, U11.33
USB_D-3: J12.D-, U15.33
USB_D-4: J15.D-, U19.33
USB_D-5: J18.D-, U23.33
USB_D-6: J21.D-, U27.33
USB_D-7: J24.D-, U31.33
USB_D-8: J27.D-, U35.33
USB_D-9: J30.D-, U39.33
USB_D-10: J33.D-, U43.33
USB_D-11: J36.D-, U47.33
VDDANA: C2.1, FB1.2, U2.6
VDDANA1: C21.1, FB2.2, U7.6
VDDANA2: C37.1, FB3.2, U11.6
VDDANA3: C53.1, FB4.2, U15.6
VDDANA4: C69.1, FB5.2, U19.6
VDDANA5: C85.1, FB6.2, U23.6
VDDANA6: C101.1, FB7.2, U27.6
VDDANA7: C117.1, FB8.2, U31.6
VDDANA8: C133.1, FB9.2, U35.6
VDDANA9: C149.1, FB10.2, U39.6
VDDANA10: C165.1, FB11.2, U43.6
VDDANA11: C181.1, FB12.2, U47.6
VDDCORE: C5.1, U2.43
VDDCORE1: C20.1, U7.43
VDDCORE2: C36.1, U11.43
VDDCORE3: C52.1, U15.43
VDDCORE4: C68.1, U19.43
VDDCORE5: C84.1, U23.43
VDDCORE6: C100.1, U27.43
VDDCORE7: C116.1, U31.43
VDDCORE8: C132.1, U35.43
VDDCORE9: C148.1, U39.43
VDDCORE10: C164.1, U43.43
VDDCORE11: C180.1, U47.43
VOUT: C6.1, C7.+, J2.EARTH, U1.1
VOUT1: C25.1, C28.+, J4.EARTH, U8.1
VOUT2: C41.1, C44.+, J7.EARTH, U12.1
VOUT3: C57.1, C60.+, J10.EARTH, U16.1
VOUT4: C73.1, C76.+, J13.EARTH, U20.1
VOUT5: C89.1, C92.+, J16.EARTH, U24.1
VOUT6: C105.1, C108.+, J19.EARTH, U28.1
VOUT7: C121.1, C124.+, J22.EARTH, U32.1
VOUT8: C137.1, C140.+, J25.EARTH, U36.1
VOUT9: C153.1, C156.+, J28.EARTH, U40.1
VOUT10: C169.1, C172.+, J31.EARTH, U44.1
VOUT11: C185.1, C188.+, J34.EARTH, U48.1
VUSB: F1.1, J1.VBUS
VUSB1: F2.1, J6.VBUS
VUSB2: F3.1, J9.VBUS
VUSB3: F4.1, J12.VBUS
VUSB4: F5.1, J15.VBUS
VUSB5: F6.1, J18.VBUS
VUSB6: F7.1, J21.VBUS
VUSB7: F8.1, J24.VBUS
VUSB8: F9.1, J27.VBUS
VUSB9: F10.1, J30.VBUS
VUSB10: F11.1, J33.VBUS
VUSB11: F12.1, J36.VBUS
V_USB: C1.1, C3.1, C8.1, D1.1, D1.2, F1.2, U1.5, U3.1, U3.3
V_USB1: C17.1, C26.1, C27.1, D12.1, D12.2, F2.2, U6.1, U6.3, U8.5
V_USB2: C33.1, C42.1, C43.1, D22.1, D22.2, F3.2, U10.1, U10.3, U12.5
V_USB3: C49.1, C58.1, C59.1, D32.1, D32.2, F4.2, U14.1, U14.3, U16.5
V_USB4: C65.1, C74.1, C75.1, D42.1, D42.2, F5.2, U18.1, U18.3, U20.5
V_USB5: C81.1, C90.1, C91.1, D52.1, D52.2, F6.2, U22.1, U22.3, U24.5
V_USB6: C97.1, C106.1, C107.1, D62.1, D62.2, F7.2, U26.1, U26.3, U28.5
V_USB7: C113.1, C122.1, C123.1, D72.1, D72.2, F8.2, U30.1, U30.3, U32.5
V_USB8: C129.1, C138.1, C139.1, D82.1, D82.2, F9.2, U34.1, U34.3, U36.5
V_USB9: C145.1, C154.1, C155.1, D92.1, D92.2, F10.2, U38.1, U38.3, U40.5
V_USB10: C161.1, C170.1, C171.1, D102.1, D102.2, F11.2, U42.1, U42.3, U44.5
V_USB11: C177.1, C186.1, C187.1, D112.1, D112.2, F12.2, U46.1, U46.3, U48.5

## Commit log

2016-06-13 Incorporate changes from Jim's protos.
2016-08-30 Initial commit of finished layout
2016-09-08 For QC review
2016-09-09 Feedback from QC review
2016-09-28 Changes due to Espressif changing chip before release
2016-10-03 Changes from design review for v02
2016-10-04 Feedback from QC review incorporated
2016-11-28 First commit of test Arduino firmware
2016-12-05 v03 - Removing RTC, I2C connector A, adding button, LED.
2016-12-06 Initial commit of firmware.
2016-12-08 initial commit of SAMD21-based director board.
2016-12-09 Cleaning up schematic
2016-12-09 Optimizing routing
2016-12-09 Stashing ESP-32 firmware.
2016-12-09 Adjusting some silkscreen.
2016-12-14 Renaming temp library file.
2016-12-14 Adding second trrs for program, usb out control
2016-12-20 Adding PROD_ID to AP2151.
2016-12-20 Added FSK demodulation hardware Changed pin assignment of FSK channel to channel with comparator Moved power switch FAULT line to a different pin
2016-12-27 FSK demodulation harware layout
2016-12-27 Minor adjustments post-engineer checklist.
2017-01-04 Test_sketch_4 works for 50+% of functionality
2017-01-09 Flash configuration 90% complete Weird thing where only N-1 of N behaviors works, though.
2017-01-10 Code checkpoint: programming works via file.
2017-01-11 Added Board class, create linked list during config file scan
2017-01-11 New board object contain channel info
2017-01-11 Generic channel handling implemented; memory leak in channel list creation
2017-01-12 Board queueing works; porting to director protos
2017-01-12 Adding UART test points, 32.768kHz RTC crystal
    - Moved flash down about 0.1" to accomodate uart test points
    - Moved SWD test points to accomodate RTC crystal
2017-01-12 Spacing test points by 2mm, increasing via drill size.
2017-01-12 post-checklist fixes - minor re-routing.
2017-01-16 FSK demodulation added
2017-01-16 Refactoring to remove cruft
2017-01-16 Adding header file guards, renamed dbt.h to i2c_registers.h
2017-01-16 Add info header to main file
2017-01-16 Remove older, unneeded prior versions and test firmwares
2017-01-18 Add checksum to file loading
2017-01-20 Added vboard boolean functions
2017-01-20 Added non-boolean virtual boards
2017-01-23 Add timer for blink LED, headers to most files
2017-02-03 Incrementing hardware to v10. No other changes.
2017-02-03 Updating silkscreen on PROG button and stat LED's
2017-02-03 Adding bottom-side arrow indicator to Direct port
2017-02-08 Mostly cleanup - Removed some commented code - Commented some debugging prints - Added some header info - Move some defines to header files - Adjusted code to remove second comparator functions - Adj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
2017-02-10 panel
2017-04-03 Minor blink code changes to fw
